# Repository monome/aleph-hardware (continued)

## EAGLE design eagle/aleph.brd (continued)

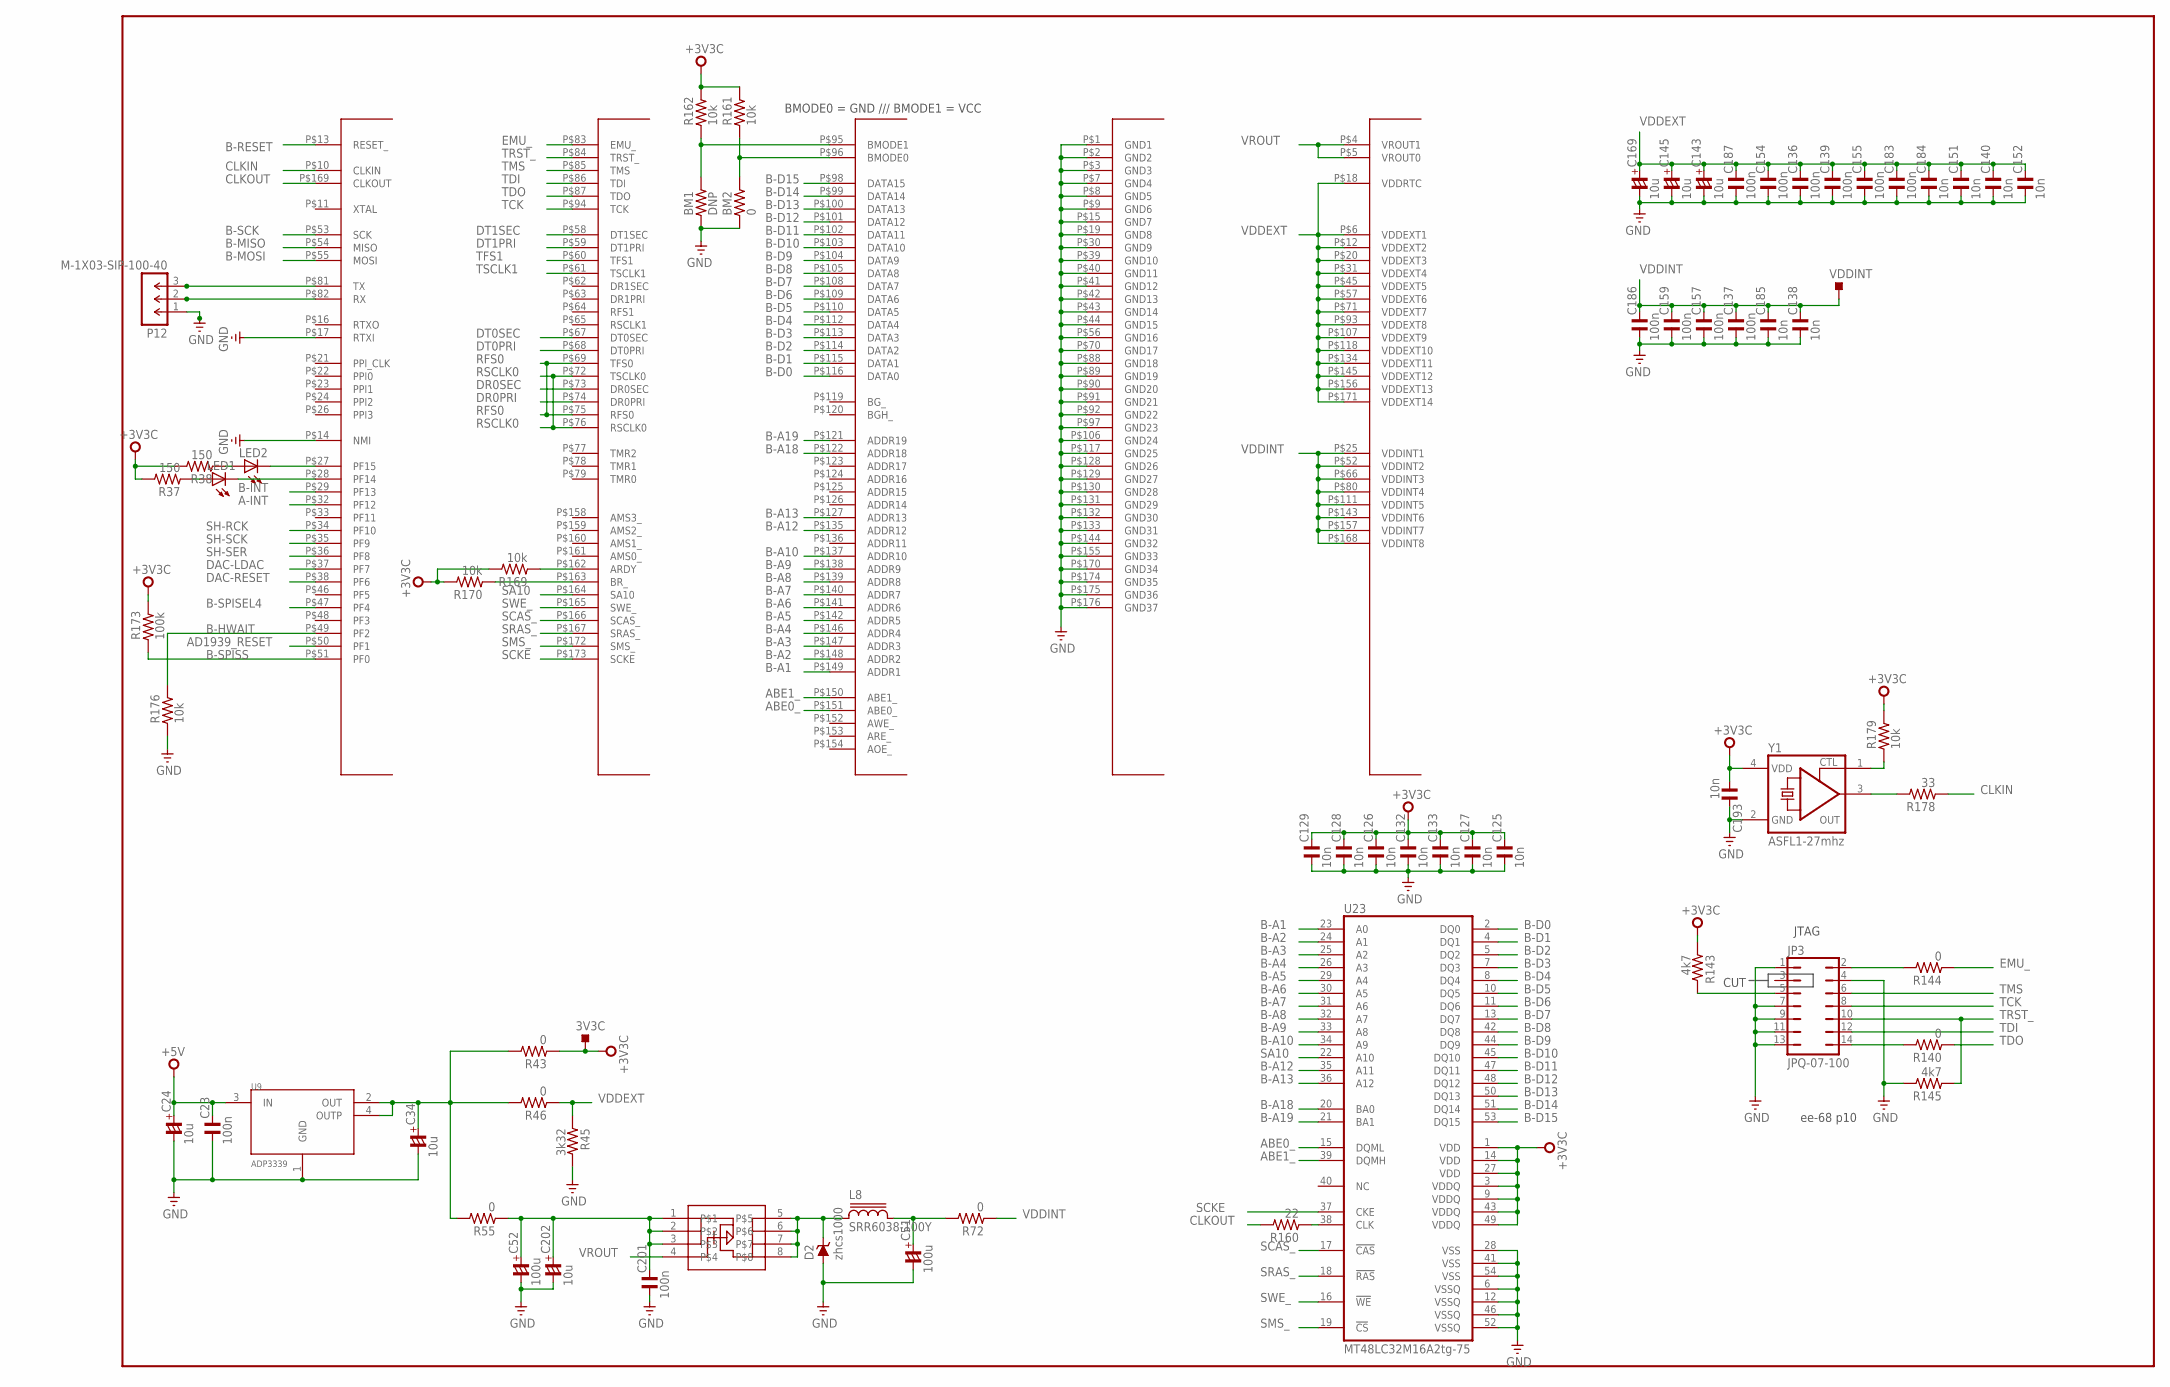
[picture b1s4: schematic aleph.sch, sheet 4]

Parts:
3V3C: TPS-SMD-15R; SMD-15R
BM1: DNP; R0603
BM2: 0; R0603
C23, C201: 100n; C1206
C24, C34, C143, C145, C169, C202: 10u; C1206/T
C51, C52: 100u; C1210/T
C125, C126, C127, C128, C129, C132, C133, C138, C140, C151, C152, C184, C185, C193: 10n; C0603
C136, C137, C139, C154, C155, C157, C159, C183, C186, C187: 100n; C0603
D2: zhcs1000; SOT23
DSP1: BF533; LQFP176
JP3: JPQ-07-100; JPQ-07
L8: SRR6038-100Y; SRR6038
LED1, LED2: LEDCHIPLED_0805; CHIPLED_0805
P12: M-1X03-SIP-100-40; SIP-100-03-40
R37, R38: 150; R0603
R43, R46, R55, R72, R140, R144: 0; R0603
R45: 3k32; R0603
R143, R145: 4k7; R0603
R160: 22; R0603
R161, R162, R169, R170, R176, R179: 10k; R0603
R173: 100k; R0603
R178: 33; R0603
U9: ADP3339; SOT223
U10: FDS9431A; SO08
U23: MT48LC32M16A2tg-75; TSOP54
VDDINT: TPS-SMD-10R; SMD-10R
Y1: ASFL1-27mhz; ASFL1

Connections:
+3V3C: 3V3C.TP, C125.2, C126.2, C127.2, C128.2, C129.2, C132.2, C133.2, C193.1, R37.2, R38.2, R43.1, R143.1, R161.2, R162.2, R169.2, R170.2, R173.2, R179.2, U23.1 (VDD), U23.3 (VDDQ), U23.9 (VDDQ), U23.14 (VDD), U23.27 (VDD), U23.43 (VDDQ), U23.49 (VDDQ), Y1.4 (VDD); also elsewhere on the board
+5V: C23.2, C24.+, U9.3 (IN); also elsewhere on the board
A-INT: DSP1.P$32 (PF12); also elsewhere on the board
ABE0_: DSP1.P$151 (ABE0_), U23.15 (DQML)
ABE1_: DSP1.P$150 (ABE1_), U23.39 (DQMH)
AD1939_RESET: DSP1.P$50 (PF1); also elsewhere on the board
B-A1: DSP1.P$149 (ADDR1), U23.23 (A0)
B-A2: DSP1.P$148 (ADDR2), U23.24 (A1)
B-A3: DSP1.P$147 (ADDR3), U23.25 (A2)
B-A4: DSP1.P$146 (ADDR4), U23.26 (A3)
B-A5: DSP1.P$142 (ADDR5), U23.29 (A4)
B-A6: DSP1.P$141 (ADDR6), U23.30 (A5)
B-A7: DSP1.P$140 (ADDR7), U23.31 (A6)
B-A8: DSP1.P$139 (ADDR8), U23.32 (A7)
B-A9: DSP1.P$138 (ADDR9), U23.33 (A8)
B-A10: DSP1.P$137 (ADDR10), U23.34 (A9)
B-A12: DSP1.P$135 (ADDR12), U23.35 (A11)
B-A13: DSP1.P$127 (ADDR13), U23.36 (A12)
B-A18: DSP1.P$122 (ADDR18), U23.20 (BA0)
B-A19: DSP1.P$121 (ADDR19), U23.21 (BA1)
B-D0: DSP1.P$116 (DATA0), U23.2 (DQ0)
B-D1: DSP1.P$115 (DATA1), U23.4 (DQ1)
B-D2: DSP1.P$114 (DATA2), U23.5 (DQ2)
B-D3: DSP1.P$113 (DATA3), U23.7 (DQ3)
B-D4: DSP1.P$112 (DATA4), U23.8 (DQ4)
B-D5: DSP1.P$110 (DATA5), U23.10 (DQ5)
B-D6: DSP1.P$109 (DATA6), U23.11 (DQ6)
B-D7: DSP1.P$108 (DATA7), U23.13 (DQ7)
B-D8: DSP1.P$105 (DATA8), U23.42 (DQ8)
B-D9: DSP1.P$104 (DATA9), U23.44 (DQ9)
B-D10: DSP1.P$103 (DATA10), U23.45 (DQ10)
B-D11: DSP1.P$102 (DATA11), U23.47 (DQ11)
B-D12: DSP1.P$101 (DATA12), U23.48 (DQ12)
B-D13: DSP1.P$100 (DATA13), U23.50 (DQ13)
B-D14: DSP1.P$99 (DATA14), U23.51 (DQ14)
B-D15: DSP1.P$98 (DATA15), U23.53 (DQ15)
B-HWAIT: DSP1.P$49 (PF2), R176.2; also elsewhere on the board
B-INT: DSP1.P$29 (PF13); also elsewhere on the board
B-MISO: DSP1.P$54 (MISO); also elsewhere on the board
B-MOSI: DSP1.P$55 (MOSI); also elsewhere on the board
B-RESET: DSP1.P$13 (RESET_); also elsewhere on the board
B-SCK: DSP1.P$53 (SCK); also elsewhere on the board
B-SPISEL4: DSP1.P$47 (PF4)
B-SPISS: DSP1.P$51 (PF0), R173.1; also elsewhere on the board
BMODE0: BM2.2, DSP1.P$96 (BMODE0), R161.1
BMODE1: BM1.2, DSP1.P$95 (BMODE1), R162.1
CLKIN: DSP1.P$10 (CLKIN), R178.1
CLKOUT: DSP1.P$169 (CLKOUT), R160.2
DAC-LDAC: DSP1.P$37 (PF7); also elsewhere on the board
DAC-RESET: DSP1.P$38 (PF6); also elsewhere on the board
DR0PRI: DSP1.P$74 (DR0PRI); also elsewhere on the board
DR0SEC: DSP1.P$73 (DR0SEC); also elsewhere on the board
DT0PRI: DSP1.P$68 (DT0PRI); also elsewhere on the board
DT0SEC: DSP1.P$67 (DT0SEC); also elsewhere on the board
DT1PRI: DSP1.P$59 (DT1PRI)
DT1SEC: DSP1.P$58 (DT1SEC); also elsewhere on the board
EMU_: DSP1.P$83 (EMU_), R144.1
GND: BM1.1, BM2.1, C23.1, C24.-, C34.-, C51.-, C52.-, C125.1, C126.1, C127.1, C128.1, C129.1, C132.1, C133.1, C136.1, C137.1, C138.1, C139.1, C140.1, C143.-, C145.-, C151.1, C152.1, C154.1, C155.1, C157.1, C159.1, C169.-, C183.1, C184.1, C185.1, C186.1, C187.1, C193.2, C201.1, C202.-, D2.1 (A), DSP1.P$1 (GND1), DSP1.P$2 (GND2), DSP1.P$3 (GND3), DSP1.P$7 (GND4), DSP1.P$8 (GND5), DSP1.P$9 (GND6), DSP1.P$14 (NMI), DSP1.P$15 (GND7), DSP1.P$17 (RTXI), DSP1.P$19 (GND8), DSP1.P$30 (GND9), DSP1.P$39 (GND10), DSP1.P$40 (GND11), DSP1.P$41 (GND12), DSP1.P$42 (GND13), DSP1.P$43 (GND14), DSP1.P$44 (GND15), DSP1.P$56 (GND16), DSP1.P$70 (GND17), DSP1.P$88 (GND18), DSP1.P$89 (GND19), DSP1.P$90 (GND20), DSP1.P$91 (GND21), DSP1.P$92 (GND22), DSP1.P$97 (GND23), DSP1.P$106 (GND24), DSP1.P$117 (GND25), DSP1.P$128 (GND26), DSP1.P$129 (GND27), DSP1.P$130 (GND28), DSP1.P$131 (GND29), DSP1.P$132 (GND30), DSP1.P$133 (GND31), DSP1.P$144 (GND32), DSP1.P$155 (GND33), DSP1.P$170 (GND34), DSP1.P$174 (GND35), DSP1.P$175 (GND36), DSP1.P$176 (GND37), JP3.1, JP3.4, JP3.7, JP3.9, JP3.11, JP3.13, P12.1, R45.2, R145.2, R176.1, U9.1 (GND), U23.6 (VSSQ), U23.12 (VSSQ), U23.28 (VSS), U23.41 (VSS), U23.46 (VSSQ), U23.52 (VSSQ), U23.54 (VSS), Y1.2 (GND); also elsewhere on the board
unnamed: C34.+, R43.2, R46.2, R55.2, U9.2 (OUT), U9.4 (OUTP)
unnamed: C52.+, C201.2, C202.+, R55.1, U10.1, U10.2, U10.3
unnamed: D2.3 (C), L8.1, U10.5, U10.6, U10.7, U10.8
unnamed: C51.+, L8.2, R72.2
unnamed: R160.1, U23.38 (CLK)
unnamed: R179.1, Y1.1 (CTL)
unnamed: JP3.2, R144.2
unnamed: JP3.5, R143.2
unnamed: DSP1.P$163 (BR_), R170.1
unnamed: JP3.14, R140.2
unnamed: DSP1.P$162 (ARDY), R169.1
unnamed: R178.2, Y1.3 (OUT)
unnamed: DSP1.P$27 (PF15), LED2.C
unnamed: DSP1.P$28 (PF14), LED1.C
unnamed: LED2.A, R38.1
unnamed: LED1.A, R37.1
unnamed: DSP1.P$81 (TX), P12.3
unnamed: DSP1.P$82 (RX), P12.2
RFS0: DSP1.P$69 (TFS0), DSP1.P$75 (RFS0); also elsewhere on the board
RSCLK0: DSP1.P$72 (TSCLK0), DSP1.P$76 (RSCLK0); also elsewhere on the board
SA10: DSP1.P$164 (SA10), U23.22 (A10)
SCAS_: DSP1.P$166 (SCAS_), U23.17 (!CAS!)
SCKE: DSP1.P$173 (SCKE), U23.37 (CKE)
SH-RCK: DSP1.P$34 (PF10)
SH-SCK: DSP1.P$35 (PF9)
SH-SER: DSP1.P$36 (PF8)
SMS_: DSP1.P$172 (SMS_), U23.19 (!CS!)
SRAS_: DSP1.P$167 (SRAS_), U23.18 (!RAS!)
SWE_: DSP1.P$165 (SWE_), U23.16 (!WE!)
TCK: DSP1.P$94 (TCK), JP3.8
TDI: DSP1.P$86 (TDI), JP3.12
TDO: DSP1.P$87 (TDO), R140.1
TFS1: DSP1.P$60 (TFS1); also elsewhere on the board
TMS: DSP1.P$85 (TMS), JP3.6
TRST_: DSP1.P$84 (TRST_), JP3.10, R145.1
TSCLK1: DSP1.P$61 (TSCLK1); also elsewhere on the board
VDDEXT: C136.2, C139.2, C140.2, C143.+, C145.+, C151.2, C152.2, C154.2, C155.2, C169.+, C183.2, C184.2, C187.2, DSP1.P$6 (VDDEXT1), DSP1.P$12 (VDDEXT2), DSP1.P$18 (VDDRTC), DSP1.P$20 (VDDEXT3), DSP1.P$31 (VDDEXT4), DSP1.P$45 (VDDEXT5), DSP1.P$57 (VDDEXT6), DSP1.P$71 (VDDEXT7), DSP1.P$93 (VDDEXT8), DSP1.P$107 (VDDEXT9), DSP1.P$118 (VDDEXT10), DSP1.P$134 (VDDEXT11), DSP1.P$145 (VDDEXT12), DSP1.P$156 (VDDEXT13), DSP1.P$171 (VDDEXT14), R45.1, R46.1
VDDINT: C137.2, C138.2, C157.2, C159.2, C185.2, C186.2, DSP1.P$25 (VDDINT1), DSP1.P$52 (VDDINT2), DSP1.P$66 (VDDINT3), DSP1.P$80 (VDDINT4), DSP1.P$111 (VDDINT5), DSP1.P$143 (VDDINT6), DSP1.P$157 (VDDINT7), DSP1.P$168 (VDDINT8), R72.1, VDDINT.TP
VROUT: DSP1.P$4 (VROUT1), DSP1.P$5 (VROUT0), U10.4

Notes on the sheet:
ee-68 p10
CUT
JTAG
BMODE0 = GND /// BMODE1 = VCC

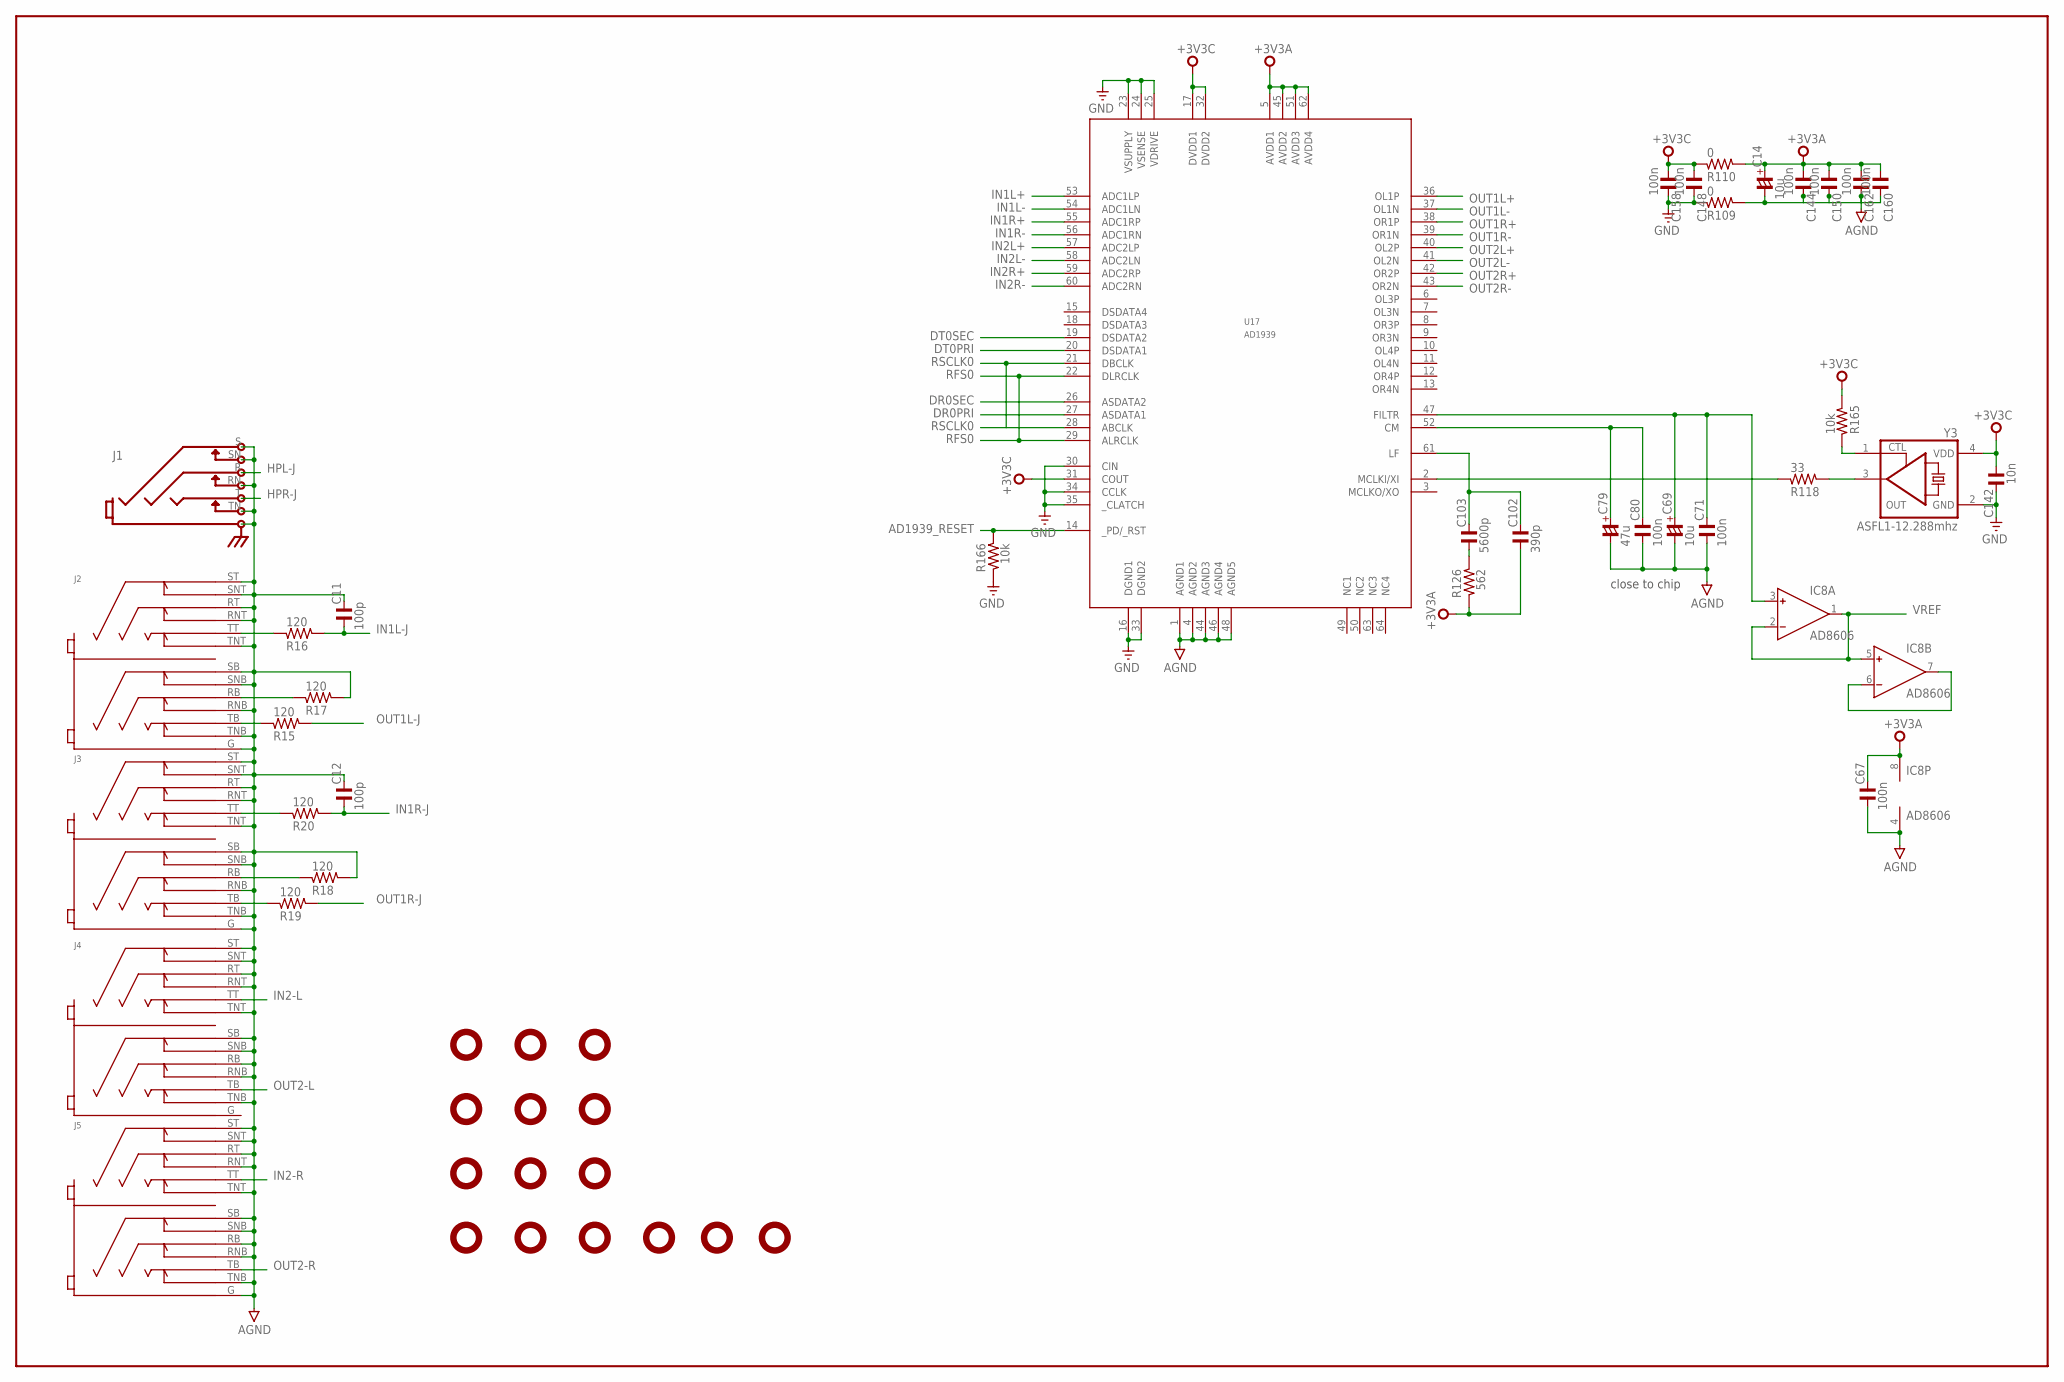
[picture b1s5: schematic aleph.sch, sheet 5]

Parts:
C11, C12: 100p; C0603
C14, C69: 10u; C1206/T
C67, C71, C80, C144, C148, C150, C158, C160, C162: 100n; C0603
C79: 47u; C1206/T
C102: 390p; C0603
C103: 5600p; C0603
C142: 10n; C0603
H1, H2, H3, H4, H5, H6, H7, H8, H9, H10, H11, H12, H13, H14, H15: MOUNT440; 120-PAD-NS
IC8: AD8606; SO8
J1: STEREOSW3GND; NEUTRIK-NRJ6HF-1
J2, J3, J4, J5: NSJ12HF
R15, R16, R17, R18, R19, R20: 120; R0603
R109, R110: 0; R0603
R118: 33; R0603
R126: 562; R0603
R165, R166: 10k; R0603
U17: AD1939; SQFP-S-10X10-64
Y3: ASFL1-12.288mhz; ASFL1

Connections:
+3V3A: C14.+, C67.2, C102.1, C144.1, C150.1, C160.1, C162.1, IC8.8 (V+), R110.2, R126.2, U17.5 (AVDD1), U17.45 (AVDD2), U17.51 (AVDD3), U17.62 (AVDD4); also elsewhere on the board
+3V3C: C142.1, C148.1, C158.1, R110.1, R165.2, U17.17 (DVDD1), U17.31 (COUT), U17.32 (DVDD2), Y3.4 (VDD); also elsewhere on the board
AD1939_RESET: R166.1, U17.14 (_PD/_RST); also elsewhere on the board
AGND: C11.2, C12.2, C14.-, C67.1, C69.-, C71.1, C79.-, C80.1, C144.2, C150.2, C160.2, C162.2, IC8.4 (V-), J1.RN, J1.S, J1.SN, J1.TN, J2.G, J2.RNB, J2.RNT, J2.RT, J2.SB, J2.SNB, J2.SNT, J2.ST, J2.TNB, J2.TNT, J3.G, J3.RNB, J3.RNT, J3.RT, J3.SB, J3.SNB, J3.SNT, J3.ST, J3.TNB, J3.TNT, J4.RB, J4.RNB, J4.RNT, J4.RT, J4.SB, J4.SNB, J4.SNT, J4.ST, J4.TNB, J4.TNT, J5.G, J5.RB, J5.RNB, J5.RNT, J5.RT, J5.SB, J5.SNB, J5.SNT, J5.ST, J5.TNB, J5.TNT, R17.2, R18.2, R109.2, U17.1 (AGND1), U17.4 (AGND2), U17.44 (AGND3), U17.46 (AGND4), U17.48 (AGND5); also elsewhere on the board
DR0PRI: U17.27 (ASDATA1); also elsewhere on the board
DR0SEC: U17.26 (ASDATA2); also elsewhere on the board
DT0PRI: U17.20 (DSDATA1); also elsewhere on the board
DT0SEC: U17.19 (DSDATA2); also elsewhere on the board
GND: C142.2, C148.2, C158.2, R109.1, R166.2, U17.16 (DGND1), U17.23 (VSUPPLY), U17.24 (VSENSE), U17.25 (VDRIVE), U17.30 (CIN), U17.33 (DGND2), U17.34 (CCLK), U17.35 (_CLATCH), Y3.2 (GND); also elsewhere on the board
HPL-J: J1.R; also elsewhere on the board
HPR-J: J1.T; also elsewhere on the board
IN1L+: U17.53 (ADC1LP); also elsewhere on the board
IN1L-: U17.54 (ADC1LN); also elsewhere on the board
IN1L-J: C11.1, R16.2; also elsewhere on the board
IN1R+: U17.55 (ADC1RP); also elsewhere on the board
IN1R-: U17.56 (ADC1RN); also elsewhere on the board
IN1R-J: C12.1, R20.2; also elsewhere on the board
IN2-L: J4.TT; also elsewhere on the board
IN2-R: J5.TT; also elsewhere on the board
IN2L+: U17.57 (ADC2LP); also elsewhere on the board
IN2L-: U17.58 (ADC2LN); also elsewhere on the board
IN2R+: U17.59 (ADC2RP); also elsewhere on the board
IN2R-: U17.60 (ADC2RN); also elsewhere on the board
unnamed: R165.1, Y3.1 (CTL)
unnamed: R118.2, Y3.3 (OUT)
unnamed: R118.1, U17.2 (MCLKI/XI)
unnamed: C69.+, C71.2, IC8.3 (IN+), U17.47 (FILTR)
unnamed: C79.+, C80.2, U17.52 (CM)
unnamed: C102.2, C103.2, U17.61 (LF)
unnamed: C103.1, R126.1
unnamed: J3.TB, R19.1
unnamed: J3.RB, R18.1
unnamed: IC8.6 (IN-), IC8.7 (OUT)
unnamed: J2.TB, R15.1
unnamed: J2.RB, R17.1
unnamed: J3.TT, R20.1
unnamed: J2.TT, R16.1
OUT1L+: U17.36 (OL1P); also elsewhere on the board
OUT1L-: U17.37 (OL1N); also elsewhere on the board
OUT1L-J: R15.2; also elsewhere on the board
OUT1R+: U17.38 (OR1P); also elsewhere on the board
OUT1R-: U17.39 (OR1N); also elsewhere on the board
OUT1R-J: R19.2; also elsewhere on the board
OUT2-L: J4.TB; also elsewhere on the board
OUT2-R: J5.TB; also elsewhere on the board
OUT2L+: U17.40 (OL2P); also elsewhere on the board
OUT2L-: U17.41 (OL2N); also elsewhere on the board
OUT2R+: U17.42 (OR2P); also elsewhere on the board
OUT2R-: U17.43 (OR2N); also elsewhere on the board
RFS0: U17.22 (DLRCLK), U17.29 (ALRCLK); also elsewhere on the board
RSCLK0: U17.21 (DBCLK), U17.28 (ABCLK); also elsewhere on the board
VREF: IC8.1 (OUT), IC8.2 (IN-), IC8.5 (IN+); also elsewhere on the board

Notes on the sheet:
close to chip

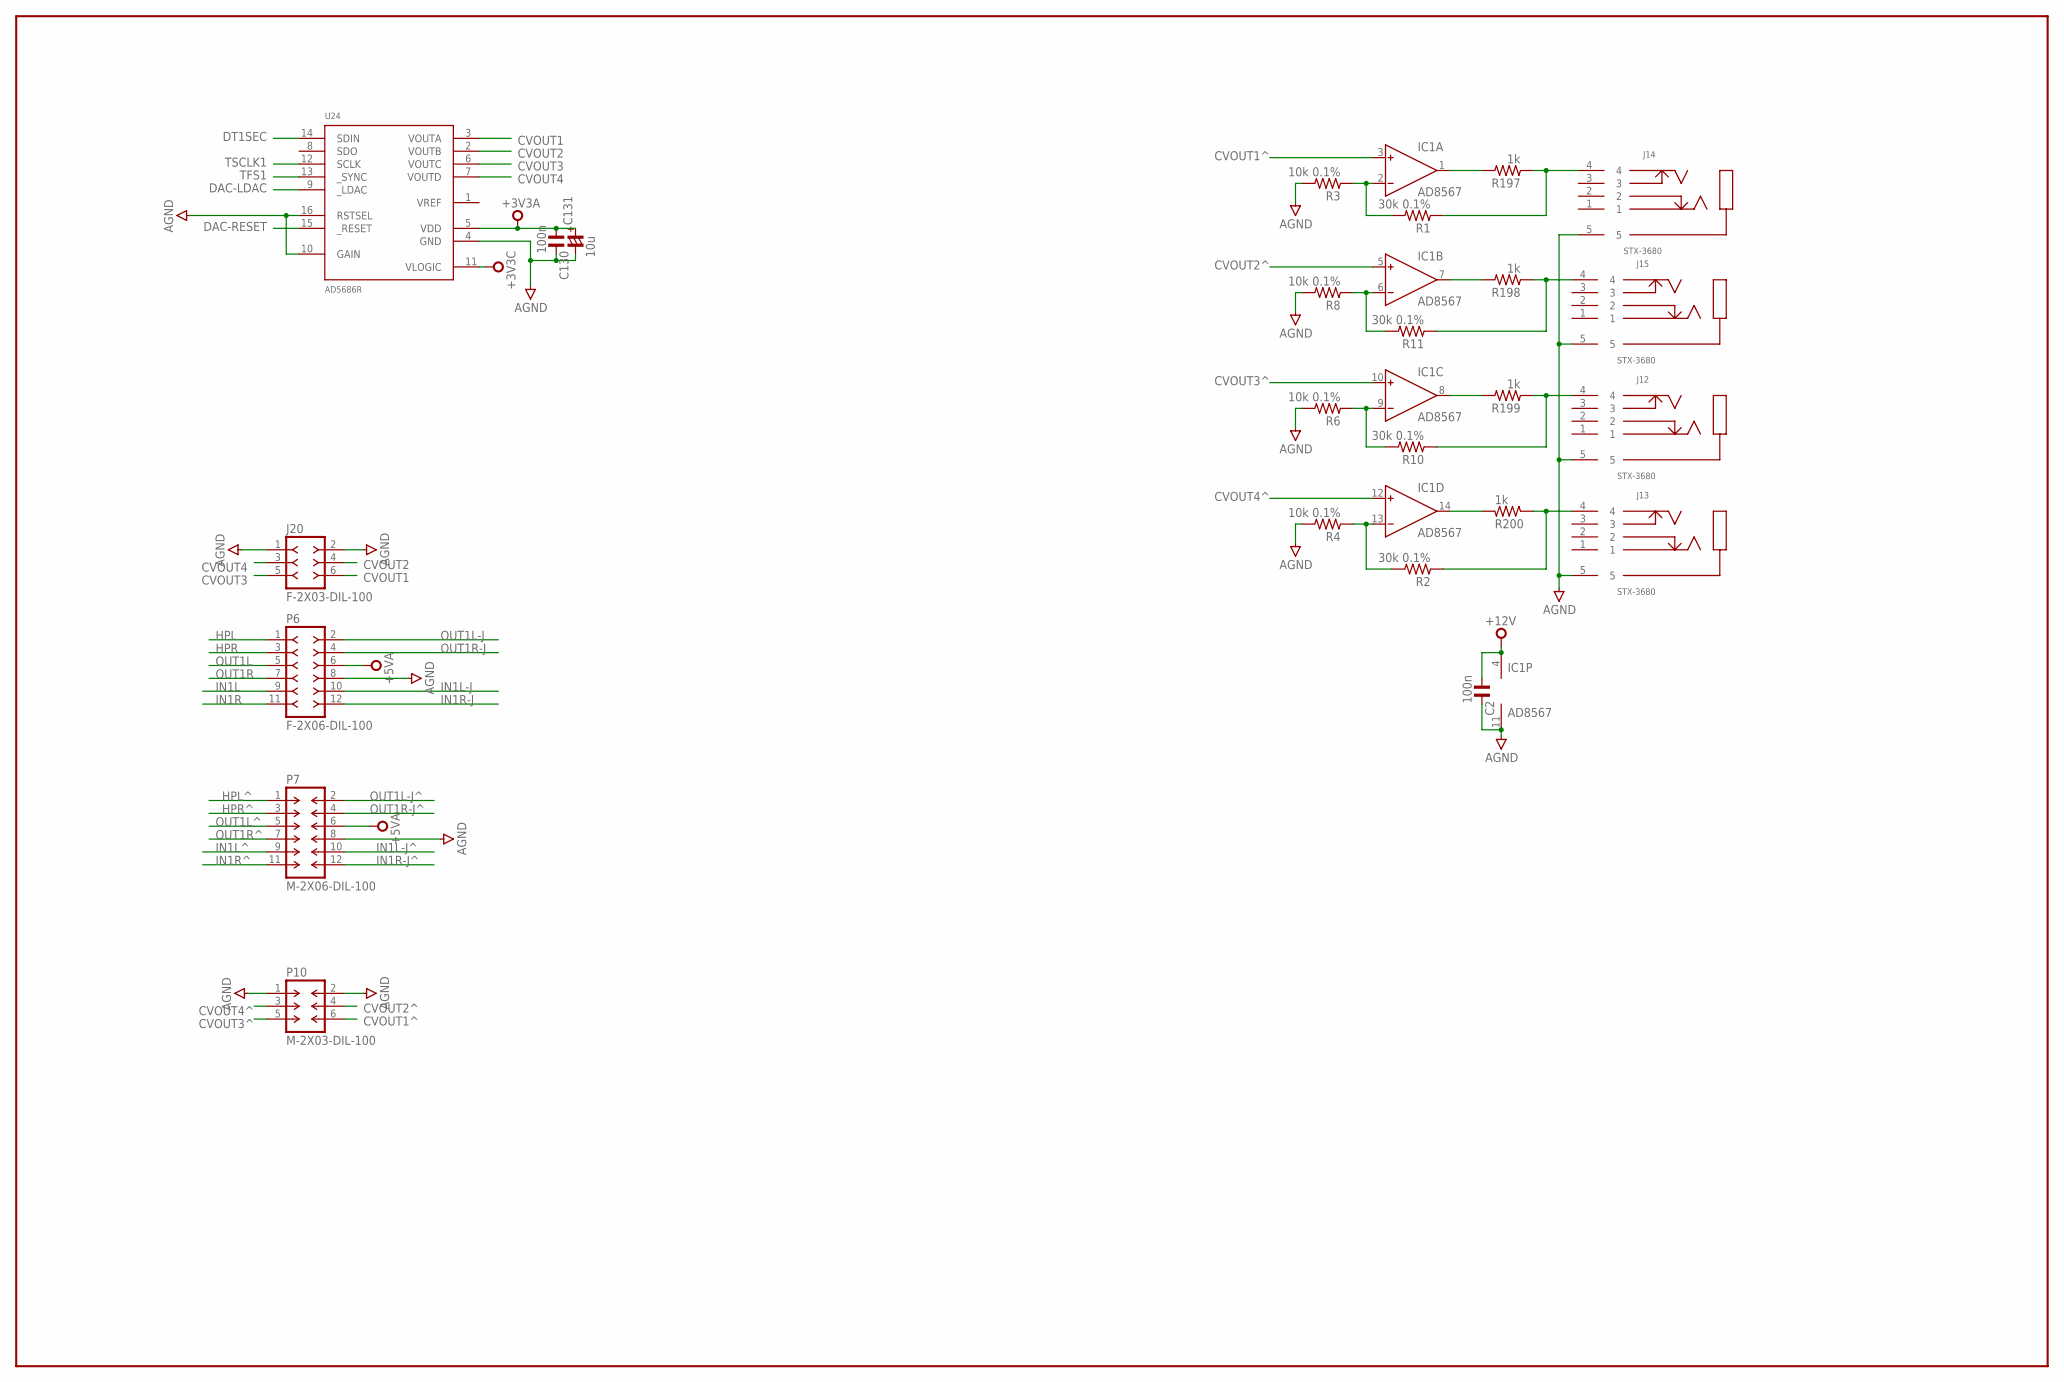
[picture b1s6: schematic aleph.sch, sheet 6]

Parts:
C2, C130: 100n; C0603
C131: 10u; C1206/T
IC1: AD8567; TSSOP14
J12, J13, J14, J15: STX-3680
J20: F-2X03-DIL-100; DIL-100-2X03
P6: F-2X06-DIL-100; DIL-100-2X06
P7: M-2X06-DIL-100; DIL-100-2X06
P10: M-2X03-DIL-100; DIL-100-2X03
R1, R2, R10, R11: 30k 0.1%; R0603
R3, R4, R6, R8: 10k 0.1%; R0603
R197, R198, R199, R200: 1k; R0603
U24: AD5686R; TSSOP16

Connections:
+3V3A: C130.1, C131.+, U24.5 (VDD); also elsewhere on the board
+3V3C: U24.11 (VLOGIC); also elsewhere on the board
+5VA: P6.6, P7.6; also elsewhere on the board
+12V: C2.1, IC1.4 (V+); also elsewhere on the board
AGND: C2.2, C130.2, C131.-, IC1.11 (V-), J12.5, J13.5, J14.5, J15.5, J20.1, J20.2, P6.8, P7.8, P10.1, P10.2, R3.2, R4.2, R6.2, R8.2, U24.4 (GND), U24.10 (GAIN), U24.16 (RSTSEL); also elsewhere on the board
CVOUT1: J20.6, U24.3 (VOUTA)
CVOUT1^: IC1.3 (IN+), P10.6
CVOUT2: J20.4, U24.2 (VOUTB)
CVOUT2^: IC1.5 (IN+), P10.4
CVOUT3: J20.5, U24.6 (VOUTC)
CVOUT3^: IC1.10 (IN+), P10.5
CVOUT4: J20.3, U24.7 (VOUTD)
CVOUT4^: IC1.12 (IN+), P10.3
DAC-LDAC: U24.9 (_LDAC); also elsewhere on the board
DAC-RESET: U24.15 (_RESET); also elsewhere on the board
DT1SEC: U24.14 (SDIN); also elsewhere on the board
HPL: P6.1; also elsewhere on the board
HPL^: P7.1; also elsewhere on the board
HPR: P6.3; also elsewhere on the board
HPR^: P7.3; also elsewhere on the board
IN1L: P6.9; also elsewhere on the board
IN1L-J: P6.10; also elsewhere on the board
IN1L-J^: P7.10; also elsewhere on the board
IN1L^: P7.9; also elsewhere on the board
IN1R: P6.11; also elsewhere on the board
IN1R-J: P6.12; also elsewhere on the board
IN1R-J^: P7.12; also elsewhere on the board
IN1R^: P7.11; also elsewhere on the board
unnamed: IC1.2 (IN-), R1.2, R3.1
unnamed: IC1.14 (OUT), R200.1
unnamed: J14.4, R1.1, R197.1
unnamed: IC1.8 (OUT), R199.2
unnamed: IC1.7 (OUT), R198.2
unnamed: IC1.6 (IN-), R8.1, R11.2
unnamed: IC1.9 (IN-), R6.1, R10.2
unnamed: IC1.13 (IN-), R2.2, R4.1
unnamed: J12.4, R10.1, R199.1
unnamed: J13.4, R2.1, R200.2
unnamed: J15.4, R11.1, R198.1
unnamed: IC1.1 (OUT), R197.2
OUT1L: P6.5; also elsewhere on the board
OUT1L-J: P6.2; also elsewhere on the board
OUT1L-J^: P7.2; also elsewhere on the board
OUT1L^: P7.5; also elsewhere on the board
OUT1R: P6.7; also elsewhere on the board
OUT1R-J: P6.4; also elsewhere on the board
OUT1R-J^: P7.4; also elsewhere on the board
OUT1R^: P7.7; also elsewhere on the board
TFS1: U24.13 (_SYNC); also elsewhere on the board
TSCLK1: U24.12 (SCLK); also elsewhere on the board

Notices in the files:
parts and their libraries:
atmel-avr: Copyright (C) 2008, Bob Starr
